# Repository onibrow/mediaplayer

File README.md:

# Mini Flac Player

Seiya Ono - Su'18

## Prototyping

I have ordered the [Adafruit VS1053 Breakout](https://www.adafruit.com/product/1381) and an Arduino Uno. This is to make sure that what I can prototype is up to my standards. I chose the Uno because of its detachable ATMegaa. [Here](https://www.arduino.cc/en/Tutorial/ArduinoToBreadboard) is a simple article about programming the ATMega over the interface.

Here is a good library I can test: [mpflaga](https://mpflaga.github.io/Arduino_Library-vs1053_for_SdFat/)

Small article with someone having trouble with `XTEST` pin: <http://www.toughdev.com/content/2013/10/interfacing-vs1053-audio-encoderdecoder-module-with-pic-using-spi/>

## Power

Because I will only be using a single cell Li-ion battery, I've went and compared a few charger/discharge protection chips, and landed with the BQ2973. It is extremely simple, only requires a few components, but does not give any sort of indication on battery level, which is the only concern I have.

Another chip I found is the [BQ24270](http://www.ti.com/product/BQ24270/technicaldocuments) made for exactly my needs.

This one has been deactivated, so I will switch over to the [BQ24297](http://www.ti.com/product/bq24297/description). An arduino library can be found [here](https://github.com/IRNAS/bq2429x).

[New LiPo Charging Circuit](https://learn.adafruit.com/adafruit-microlipo-and-minilipo-battery-chargers/downloads)

### Datasheets

[VS1053](https://cdn-shop.adafruit.com/datasheets/vs1053.pdf)

[ATmega328P](http://ww1.microchip.com/downloads/en/DeviceDoc/Atmel-42735-8-bit-AVR-Microcontroller-ATmega328-328P_Datasheet.pdf)

[BQ2973](http://www.ti.com/lit/ds/symlink/bq2973.pdf)

[CSD16301Q2](http://www.ti.com/lit/ds/symlink/csd16301q2.pdf)

[BQ24297](http://www.ti.com/lit/ds/symlink/bq24297.pdf)

[MCP73831T](https://www.digikey.com/product-detail/en/microchip-technology/MCP73831T-2ACI-OT/MCP73831T-2ACI-OTCT-ND/1979802)

### BOM

Mega Chip mount: <https://www.digikey.com/products/en?keywords=ED3128-ND>

VS1053: <https://www.digikey.com/product-detail/en/adafruit-industries-llc/1681/1528-2645-ND/>

ATMega328: <https://www.digikey.com/product-detail/en/microchip-technology/ATMEGA328PB-AUR/ATMEGA328PB-AURCT-ND/5722706>

Codec Crystal: <https://www.digikey.com/product-detail/en/abracon-llc/ABM8G-12.288MHZ-18-D2Y-T/535-10262-1-ND/2218075>

Buttons: <https://www.digikey.com/product-detail/en/e-switch/TL1105LF160Q/EG2505-ND/378971> <https://www.digikey.com/product-detail/en/e-switch/TL1105LF250Q/EG2506-ND/378972>

### Assembly

I need to only do the microcontroller and peripherals first, so I can power it using 5V and flash it with the bootloader (no regulator).

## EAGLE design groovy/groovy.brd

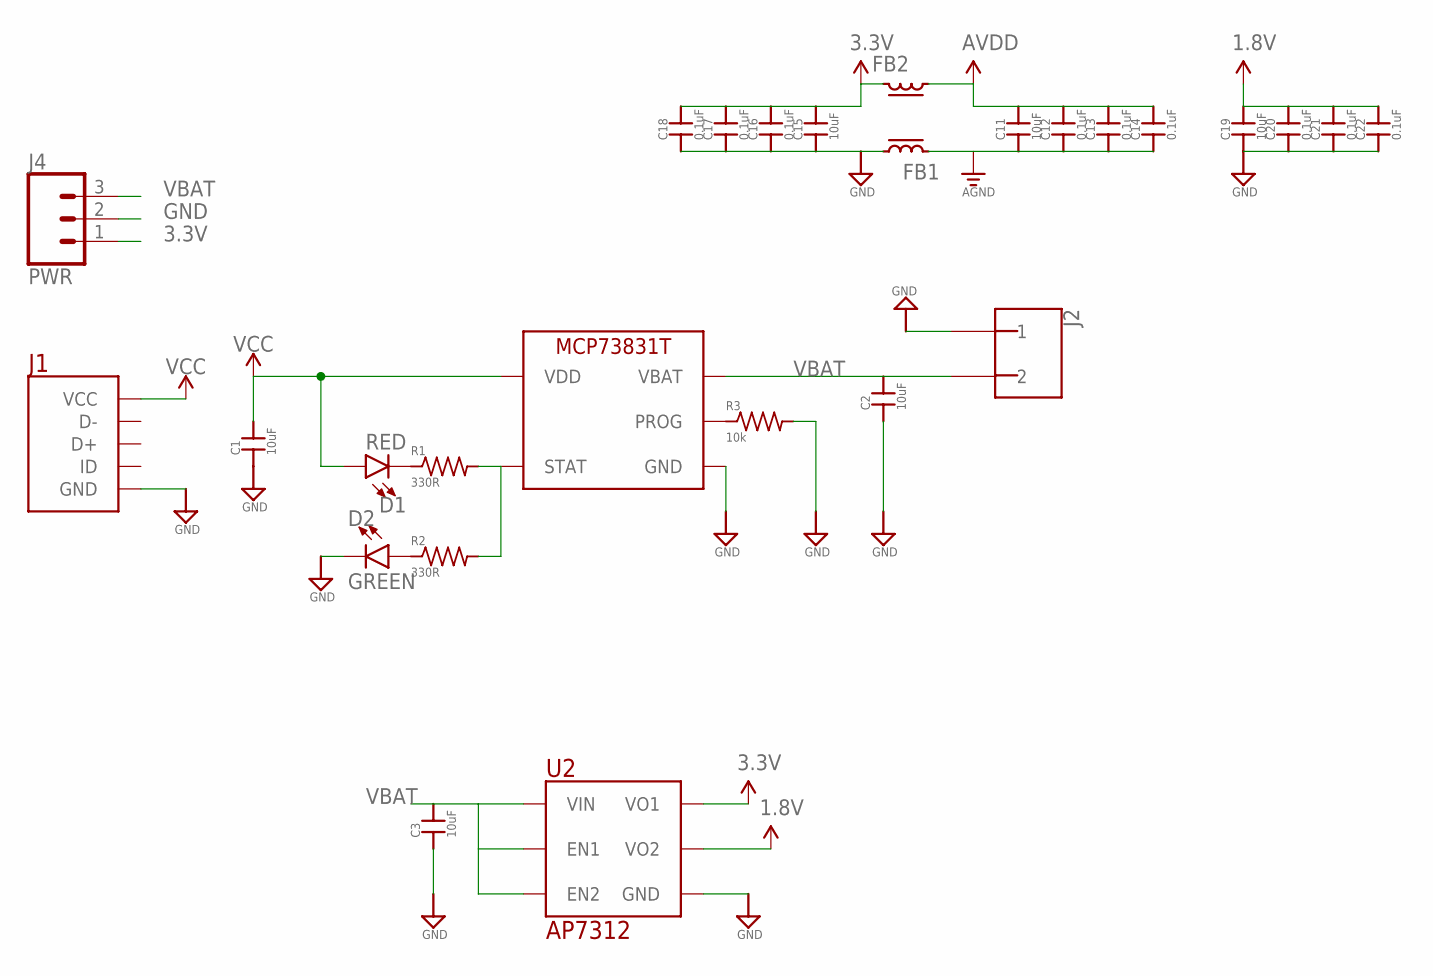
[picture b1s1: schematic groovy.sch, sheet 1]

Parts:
C1, C2, C3, C11, C15, C19: 10uF; 0402-CAP
C12, C13, C14, C16, C17, C18, C20, C21, C22: 0.1uF; 0402-CAP
D1: RED; LED-0603
D2: GREEN; LED-0603
FB1, FB2: FERRITE; 0603-FERR
J1: USB_MICRO
J2: 2_PIN_JST-XH
J4: PWR; 1X03
R1, R2: 330R; R0603
R3: 10k; R0603
U1: MCP73831T; SOT23-5
U2: AP7312-1833; 6-SOT

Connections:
1.8V: C19.2, C20.2, C21.2, C22.2, U2.1 (VO2); also elsewhere on the board
3.3V: C15.2, C16.2, C17.2, C18.2, FB2.2, J4.1, U2.6 (VO1); also elsewhere on the board
AGND: C11.1, C12.1, C13.1, C14.1, FB1.2; also elsewhere on the board
AVDD: C11.2, C12.2, C13.2, C14.2, FB2.1; also elsewhere on the board
GND: C1.1, C2.1, C3.1, C15.1, C16.1, C17.1, C18.1, C19.1, C20.1, C21.1, C22.1, D2.C, FB1.1, J1.GND, J2.P$1 (1), J4.2, R3.2, U1.2 (GND), U2.2 (GND); also elsewhere on the board
unnamed: D1.C, R1.1
unnamed: D2.A, R2.1
unnamed: R1.2, R2.2, U1.1 (STAT)
unnamed: R3.1, U1.5 (PROG)
VBAT: C2.2, C3.2, J2.P$2 (2), J4.3, U1.3 (VBAT), U2.3 (EN2), U2.4 (EN1), U2.5 (VIN)
VCC: C1.2, D1.A, J1.VCC, U1.4 (VDD)

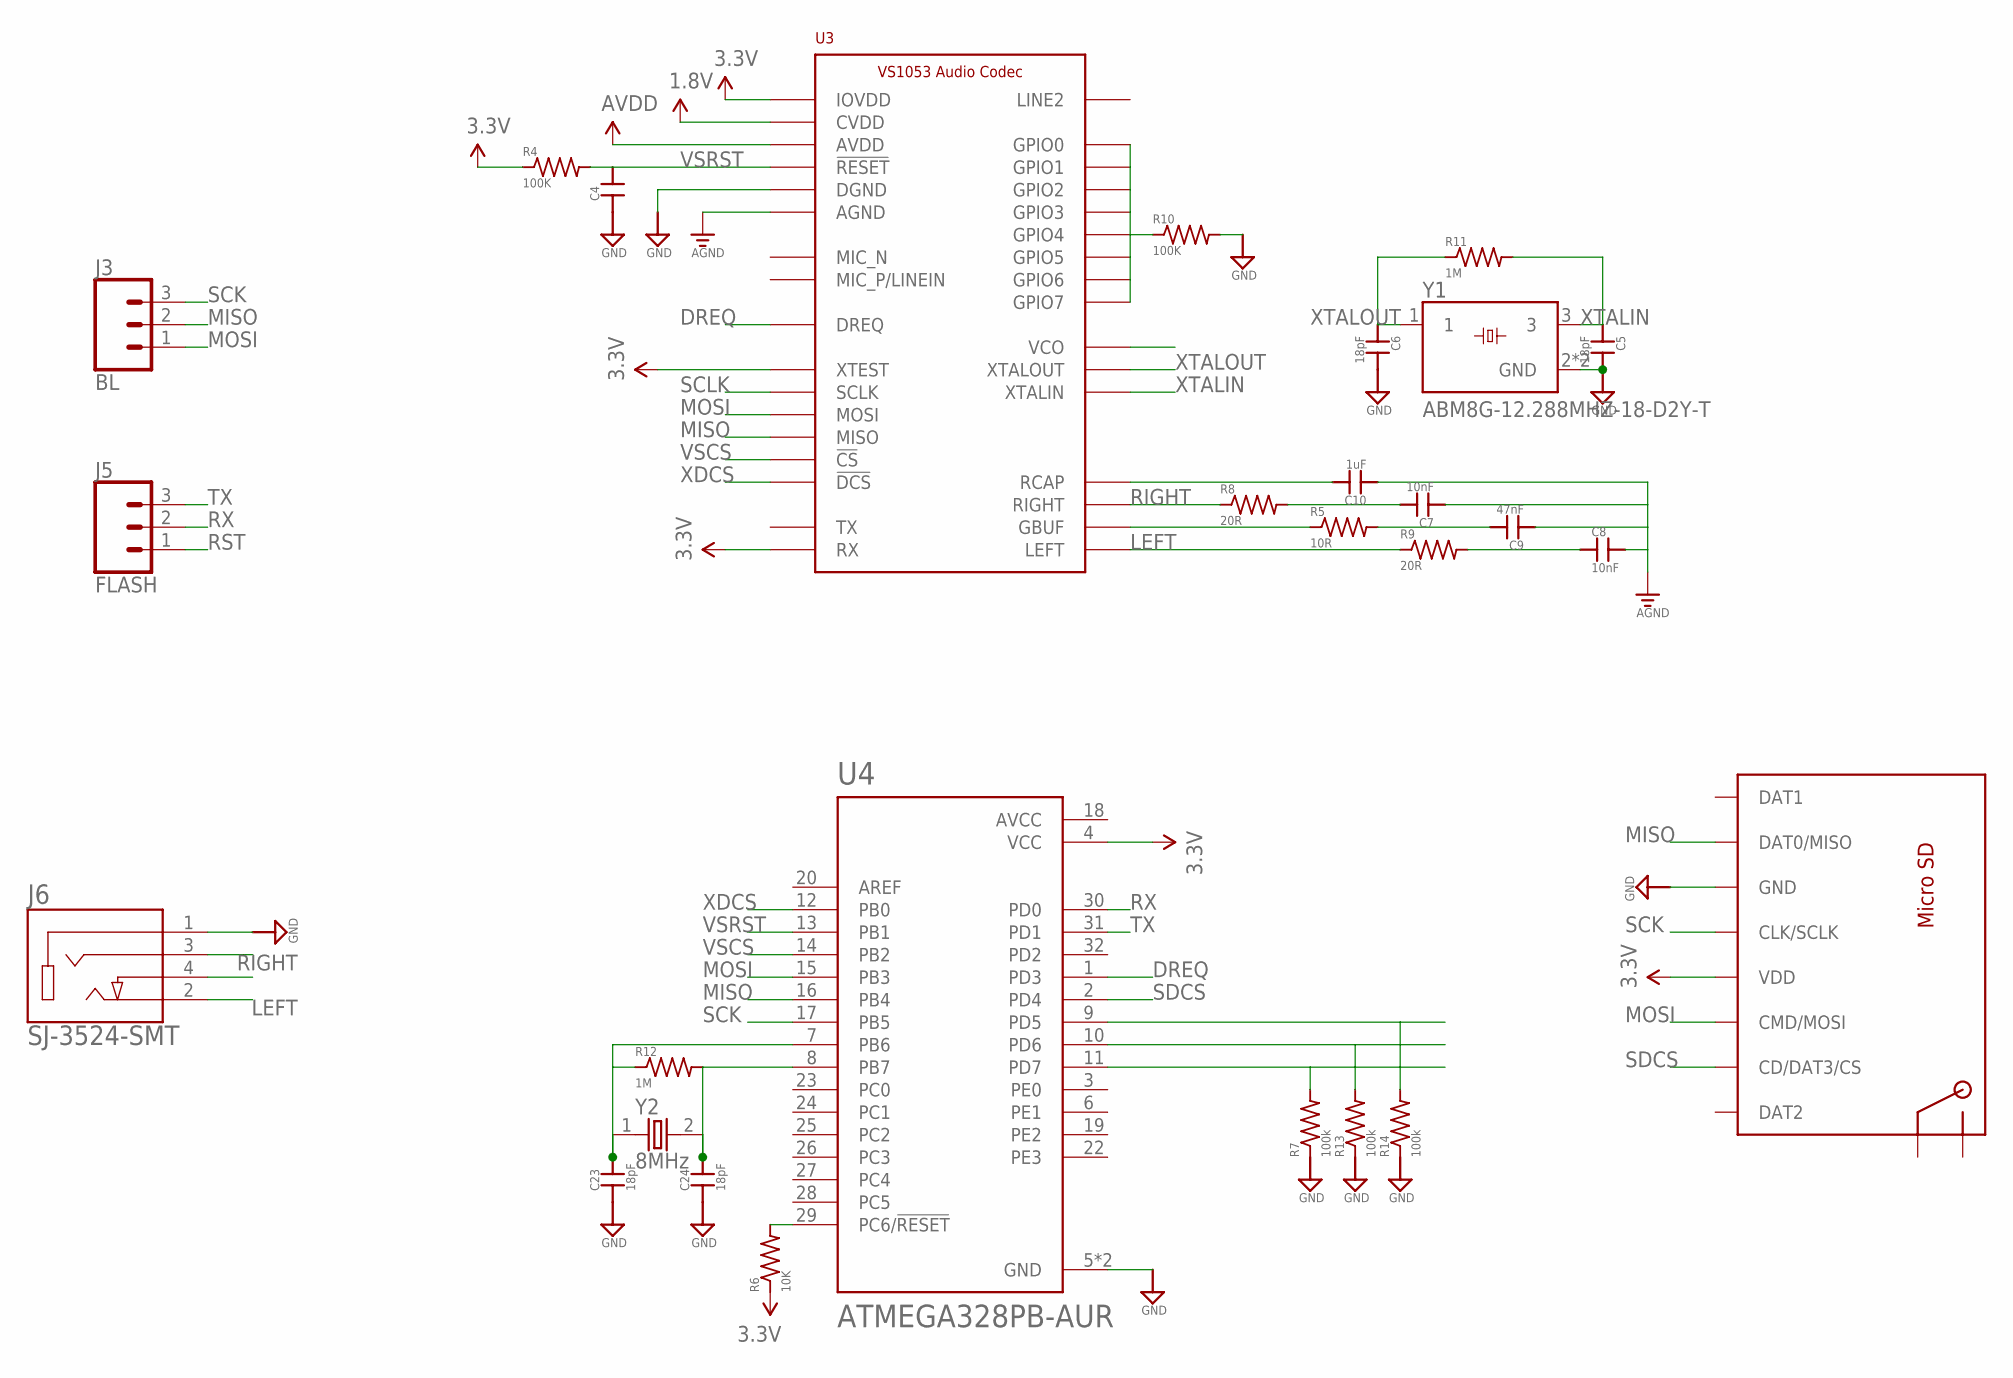
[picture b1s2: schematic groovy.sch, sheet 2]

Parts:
C4: CAP0603-CAP; 0603-CAP
C5, C6, C23, C24: 18pF; 0603-CAP
C7, C8: 10nF; 0603-CAP
C9: 47nF; 0603-CAP
C10: 1uF; 0603-CAP
J3: BL; 1X03
J5: FLASH; 1X03
J6: SJ-3524-SMT; CUI_SJ-3524-SMT
P1: MICROSD
R4, R10: 100K; R0603
R5: 10R; R0603
R6: 10K; R0603
R7, R13, R14: 100k; R0603
R8, R9: 20R; R0603
R11, R12: 1M; R0603
U3: VS1053; QFP50P900X900X120-48N
U4: ATMEGA328PB-AUR; QFP80P900X900X120-32N
Y1: ABM8G-12.288MHZ-18-D2Y-T; OSCSC320X250X100N
Y2: 8MHz; XTAL500X320X130N

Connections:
1.8V: U3.5 (CVDD), U3.7 (CVDD), U3.24 (CVDD), U3.31 (CVDD); also elsewhere on the board
3.3V: P1.4 (VDD), R4.1, R6.1, U3.6 (IOVDD), U3.14 (IOVDD), U3.19 (IOVDD), U3.26 (RX), U3.32 (XTEST), U4.4 (VCC); also elsewhere on the board
AGND: C7.1, C8.2, C9.1, C10.1, U3.37 (AGND), U3.40 (AGND), U3.41 (AGND), U3.47 (AGND); also elsewhere on the board
AVCC: U4.18 (AVCC)
AVDD: U3.38 (AVDD), U3.43 (AVDD), U3.45 (AVDD); also elsewhere on the board
DREQ: U3.8 (DREQ), U4.1 (PD3)
GBUF: R5.1, U3.42 (GBUF)
GND: C4.1, C5.2, C6.2, C23.1, C24.1, J6.1, P1.6 (GND), R7.1, R10.2, R13.1, R14.1, U3.4 (DGND), U3.16 (DGND), U3.20 (DGND), U3.21 (DGND), U3.22 (DGND), U3.35 (DGND), U4.5 (GND), U4.21 (GND), Y1.2 (GND), Y1.4 (GND); also elsewhere on the board
LEFT: J6.2, R9.1, U3.46 (LEFT)
MISO: J3.2, P1.7 (DAT0/MISO), U3.30 (MISO), U4.16 (PB4)
MOSI: J3.1, P1.3 (CMD/MOSI), U3.29 (MOSI), U4.15 (PB3)
unnamed: C7.2, R8.2
unnamed: C23.2, R12.1, U4.7 (PB6), Y2.1
unnamed: R7.2, U4.11 (PD7)
unnamed: C24.2, R12.2, U4.8 (PB7), Y2.2
unnamed: R13.2, U4.10 (PD6)
unnamed: R14.2, U4.9 (PD5)
unnamed: C9.2, R5.2
unnamed: C8.1, R9.2
unnamed: R10.1, U3.9 (GPIO2), U3.10 (GPIO3), U3.11 (GPIO6), U3.12 (GPIO7), U3.25 (GPIO5), U3.33 (GPIO0), U3.34 (GPIO1), U3.36 (GPIO4)
RCAP: C10.2, U3.44 (RCAP)
RIGHT: J6.3, R8.1, U3.39 (RIGHT)
RST: J5.1, R6.2, U4.29 (PC6/!RESET)
RX: J5.2, U4.30 (PD0)
SCK: J3.3, P1.5 (CLK/SCLK), U4.17 (PB5)
SCLK: U3.28 (SCLK)
SDCS: P1.2 (CD/DAT3/CS), U4.2 (PD4)
TX: J5.3, U4.31 (PD1)
VSCS: U3.23 (!CS!), U4.14 (PB2)
VSRST: C4.2, R4.2, U3.3 (!RESET!), U4.13 (PB1)
XDCS: U3.13 (!DCS!), U4.12 (PB0)
XTALIN: C5.1, R11.2, U3.18 (XTALIN), Y1.3
XTALOUT: C6.1, R11.1, U3.17 (XTALOUT), Y1.1

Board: 2 copper layers, 55 parts (0 on the bottom side), 37 nets, no tracks yet.

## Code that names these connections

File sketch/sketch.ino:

// include SPI, MP3 and SD libraries
#include <SPI.h>
#include <Adafruit_VS1053.h>
#include <SD.h>

#define BREAKOUT_RESET  7 // 9      // VS1053 reset pin (output)                   // PB1 DNE -> GPIO 5 = Pin 7
#define BREAKOUT_CS     10     // VS1053 chip select pin (output)             // PB2 Ex = SS       = Pin 10
#define BREAKOUT_DCS    8      // VS1053 Data/command select pin (output)     // PB0 Ex = GPIO 6   = Pin 8
//#define SHIELD_CS     7      // VS1053 chip select pin (output)
//#define SHIELD_DCS    6      // VS1053 Data/command select pin (output)

// These are common pins between breakout and shield
#define CARDCS 6 // 4     // Card chip select pin                                  // PD4 DNE -> GPIO 4 = Pin 6
// DREQ should be an Int pin, see http://arduino.cc/en/Reference/attachInterrupt
#define DREQ 5 // 3       // VS1053 Data request, ideally an Interrupt pin         // PD3 DNE -> GPIO 3 = Pin 5

Adafruit_VS1053_FilePlayer musicPlayer =
  Adafruit_VS1053_FilePlayer(BREAKOUT_RESET, BREAKOUT_CS, BREAKOUT_DCS, DREQ, CARDCS);
int start_sig = 0;

void setup() {
  Serial.begin(9600);
  pinMode(14, INPUT);


  if (! musicPlayer.begin()) {
    while (1);
  }

  if (!SD.begin(CARDCS)) {
    Serial.println(F("SD failed, or not present"));
    while (1);  // don't do anything more
  }

  // list files
  SD.open("/");

  // Set volume for left, right channels. lower numbers == louder volume!
  musicPlayer.setVolume(10, 10);

  // Timer interrupts are not suggested, better to use DREQ interrupt!
  //musicPlayer.useInterrupt(VS1053_FILEPLAYER_TIMER0_INT); // timer int

  // If DREQ is on an interrupt pin (on uno, #2 or #3) we can do background
  // audio playing
  //  musicPlayer.useInterrupt(VS1053_FILEPLAYER_PIN_INT);  // DREQ int

  // Play one file, don't return until complete
  //  Serial.println(F("Playing FLAC"));
  //  musicPlayer.playFullFile("track1~1.fla");
  // Play another file in the background, REQUIRES interrupts!
  //  Serial.println(F("Playing MP3"));

}

void loop() {
  // File is playing in the background
  start_sig = digitalRead(14);
  if (musicPlayer.stopped() && start_sig == 1) {
    musicPlayer.playFullFile("sugar.mp3");
  }
  delay(100);
  //  if (musicPlayer.stopped()) {
  //    Serial.println("Done playing music");
  //    while (1) {
  //      delay(10);  // we're done! do nothing...
  //    }
  //  }

  //  if (Serial.available()) {
  //    char c = Serial.read();
  //
  //    // if we get an 's' on the serial console, stop!
  //    if (c == 's') {
  //      musicPlayer.stopPlaying();
  //    }
  //
  //    // if we get an 'p' on the serial console, pause/unpause!
  //    if (c == 'p') {
  //      if (! musicPlayer.paused()) {
  //        Serial.println("Paused");
  //        musicPlayer.pausePlaying(true);
  //      } else {
  //        Serial.println("Resumed");
  //        musicPlayer.pausePlaying(false);
  //      }
  //    }
  //  }

  delay(10);
}


/// File listing helper
void printDirectory(File dir, int numTabs) {
  while (true) {

    File entry =  dir.openNextFile();
    if (! entry) {
      // no more files
      //Serial.println("**nomorefiles**");
      break;
    }
    for (uint8_t i = 0; i < numTabs; i++) {
      Serial.print('\t');
    }
    Serial.print(entry.name());
    if (entry.isDirectory()) {
      Serial.println("/");
      printDirectory(entry, numTabs + 1);
    } else {
      // files have sizes, directories do not
      Serial.print("\t\t");
      Serial.println(entry.size(), DEC);
    }
    entry.close();
  }
}

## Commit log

2018-07-03 start project
2018-07-10 find a good example
2018-07-10 add some debugging - need to figure out dreq hi
2018-07-29 find some good documentaoitn
2018-08-16 Add charger
2018-08-17 blah
2018-08-26 add library and add more links
2018-08-27 start schem
2018-08-27 add gitignore
2018-08-27 fix gitignore for eagle files
2018-10-03 add adas1000
2018-12-02 move library to dot files
2018-12-19 remove old stuff, make some progress on power
2018-12-20 do more audio stuff
2018-12-24 do more work on schem - need to add microphone
2019-11-28 left over commit
2019-11-29 add code for 149 proj
